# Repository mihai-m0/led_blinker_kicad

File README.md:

# 555 Timer LED Blinker

A simple astable 555 timer circuit that blinks an LED at about 1 Hz,
designed in KiCad as my first PCB project.

## Overview
- 2-layer through-hole PCB, 50 x 40 mm
- Powered by a 9V battery
- Blink frequency: f = 1.44 / ((R1 + 2·R2) · C1) ≈ 1 Hz

## Schematic

## Bill of Materials
| Ref | Value | Footprint |
|-----|-------|-----------|
| U1 | NE555P | DIP-8 |
| R1 | 10k | Axial 0207 |
| R2 | 68k | Axial 0207 |
| R3 | 470 | Axial 0207 |
| C1 | 10µF electrolytic | Radial D5.0 |
| C2 | 10nF | Disc 5mm |
| C3 | 100nF | Disc 5mm |
| D1 | Red LED | 5mm |
| J1 | 2-pin header | 2.54mm |

## How it works
C1 charges through R1 and R2 and discharges through R2. The 555 switches
its output when C1 reaches 1/3 and 2/3 of the supply voltage.

## What I learned
- Schematic capture, footprint assignment, and ERC
- 2-layer PCB layout, routing, and ground pour

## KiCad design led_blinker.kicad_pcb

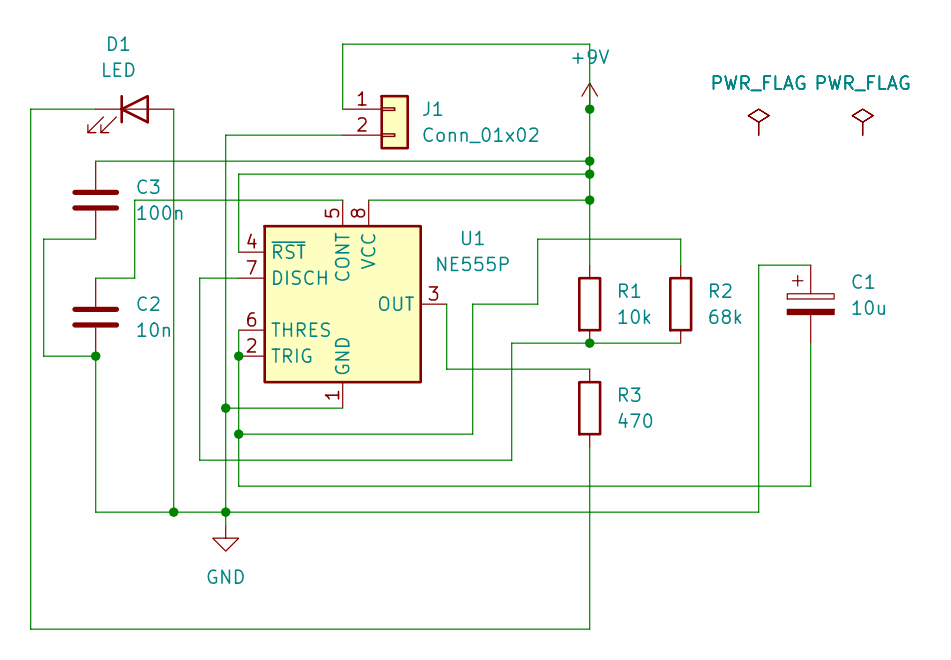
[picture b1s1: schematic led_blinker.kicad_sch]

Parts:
C1: 10u; CP_Radial_D5.0mm_P2.00mm
C2: 10n; C_Disc_D5.0mm_W2.5mm_P5.00mm
C3: 100n; C_Disc_D5.0mm_W2.5mm_P5.00mm
D1: LED; LED_D5.0mm
J1: Conn_01x02; PinHeader_1x02_P2.54mm_Vertical
R1: 10k; R_Axial_DIN0207_L6.3mm_D2.5mm_P10.16mm_Horizontal
R2: 68k; R_Axial_DIN0207_L6.3mm_D2.5mm_P10.16mm_Horizontal
R3: 470; R_Axial_DIN0207_L6.3mm_D2.5mm_P10.16mm_Horizontal
U1: NE555P; DIP-8_W7.62mm

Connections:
+9V: C3.1, J1.1, R1.1, U1.4 (~RST), U1.8 (VCC)
GND: C1.1, C2.2, C3.2, D1.2 (A), J1.2, U1.1 (GND)
unnamed: D1.1 (K), R3.2
unnamed: C2.1, U1.5 (CONT)
unnamed: R1.2, R2.2, U1.7 (DISCH)
unnamed: R3.1, U1.3 (OUT)
unnamed: C1.2, R2.1, U1.2 (TRIG), U1.6 (THRES)

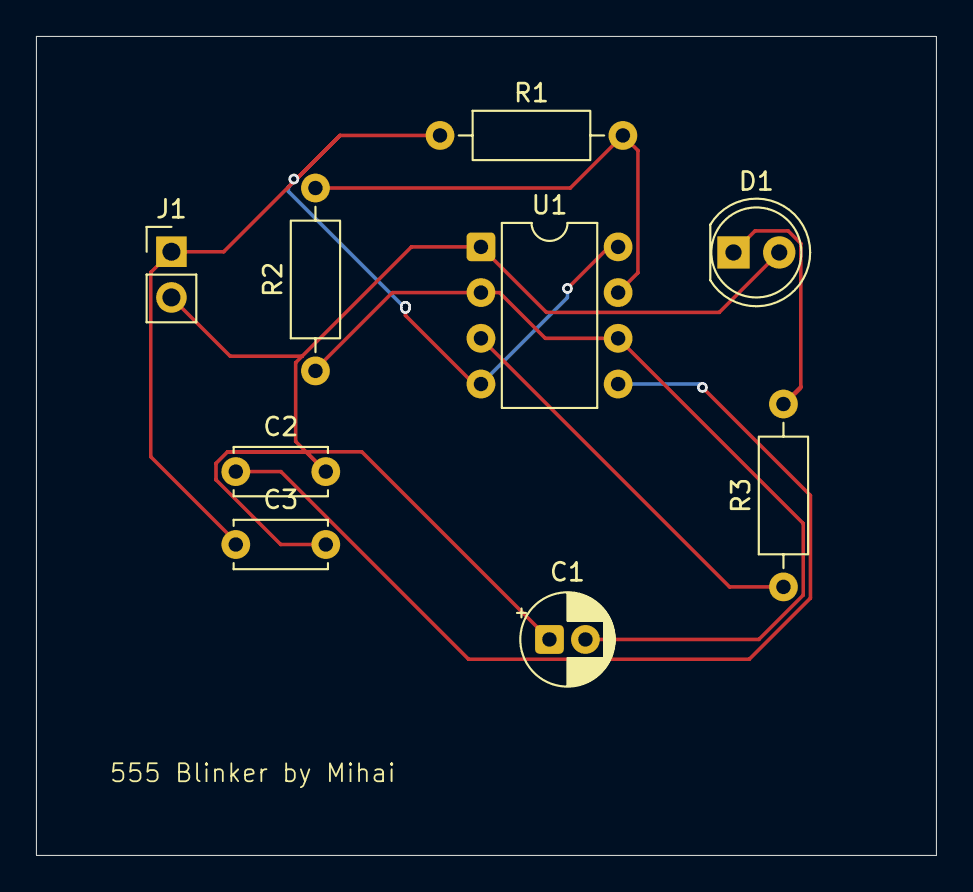
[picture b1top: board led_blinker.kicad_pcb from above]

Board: 2 copper layers, 50.0 x 45.5 mm, 9 parts (0 on the bottom side), 7 nets.
